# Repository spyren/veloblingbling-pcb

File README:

Electronic Design for the Velo Bling-Bling Project
**************************************************

http://veloblingbling.ch

LED lights for bicycle wheels.
16 multi color LEDs on each side (PCB top- and bottom side).
There are two windows (upper and lower) on each side for display dynamic
information like speed, trip time, trip distance, etc. or static information
like strings and images.

The Printed Circuit Board (PCB) is free hardware.
The PCB is a multi-layer (4 layer) 160 x 30.5 x 1.6 mm FR4 board.
The firmware for the MK22DX256VLF5 MCU is also on GitHub:
https://github.com/spyren/veloblingbling-mcu

There is also an optional Bluetooth Low Energy (Smart) subsystem on board.
It is a LAIRD BL600-SA module. The Bluetooth application software is on GitHub
too:
https://github.com/spyren/veloblingbling-ble

It is possible to mount die PCB direct onto the wheel spokes but it is better
to use a mounting frame. This frame can be ordered from http://shapeways.com
or you can print it by yourself on 3D printer.
https://github.com/spyren/veloblingbling-frame

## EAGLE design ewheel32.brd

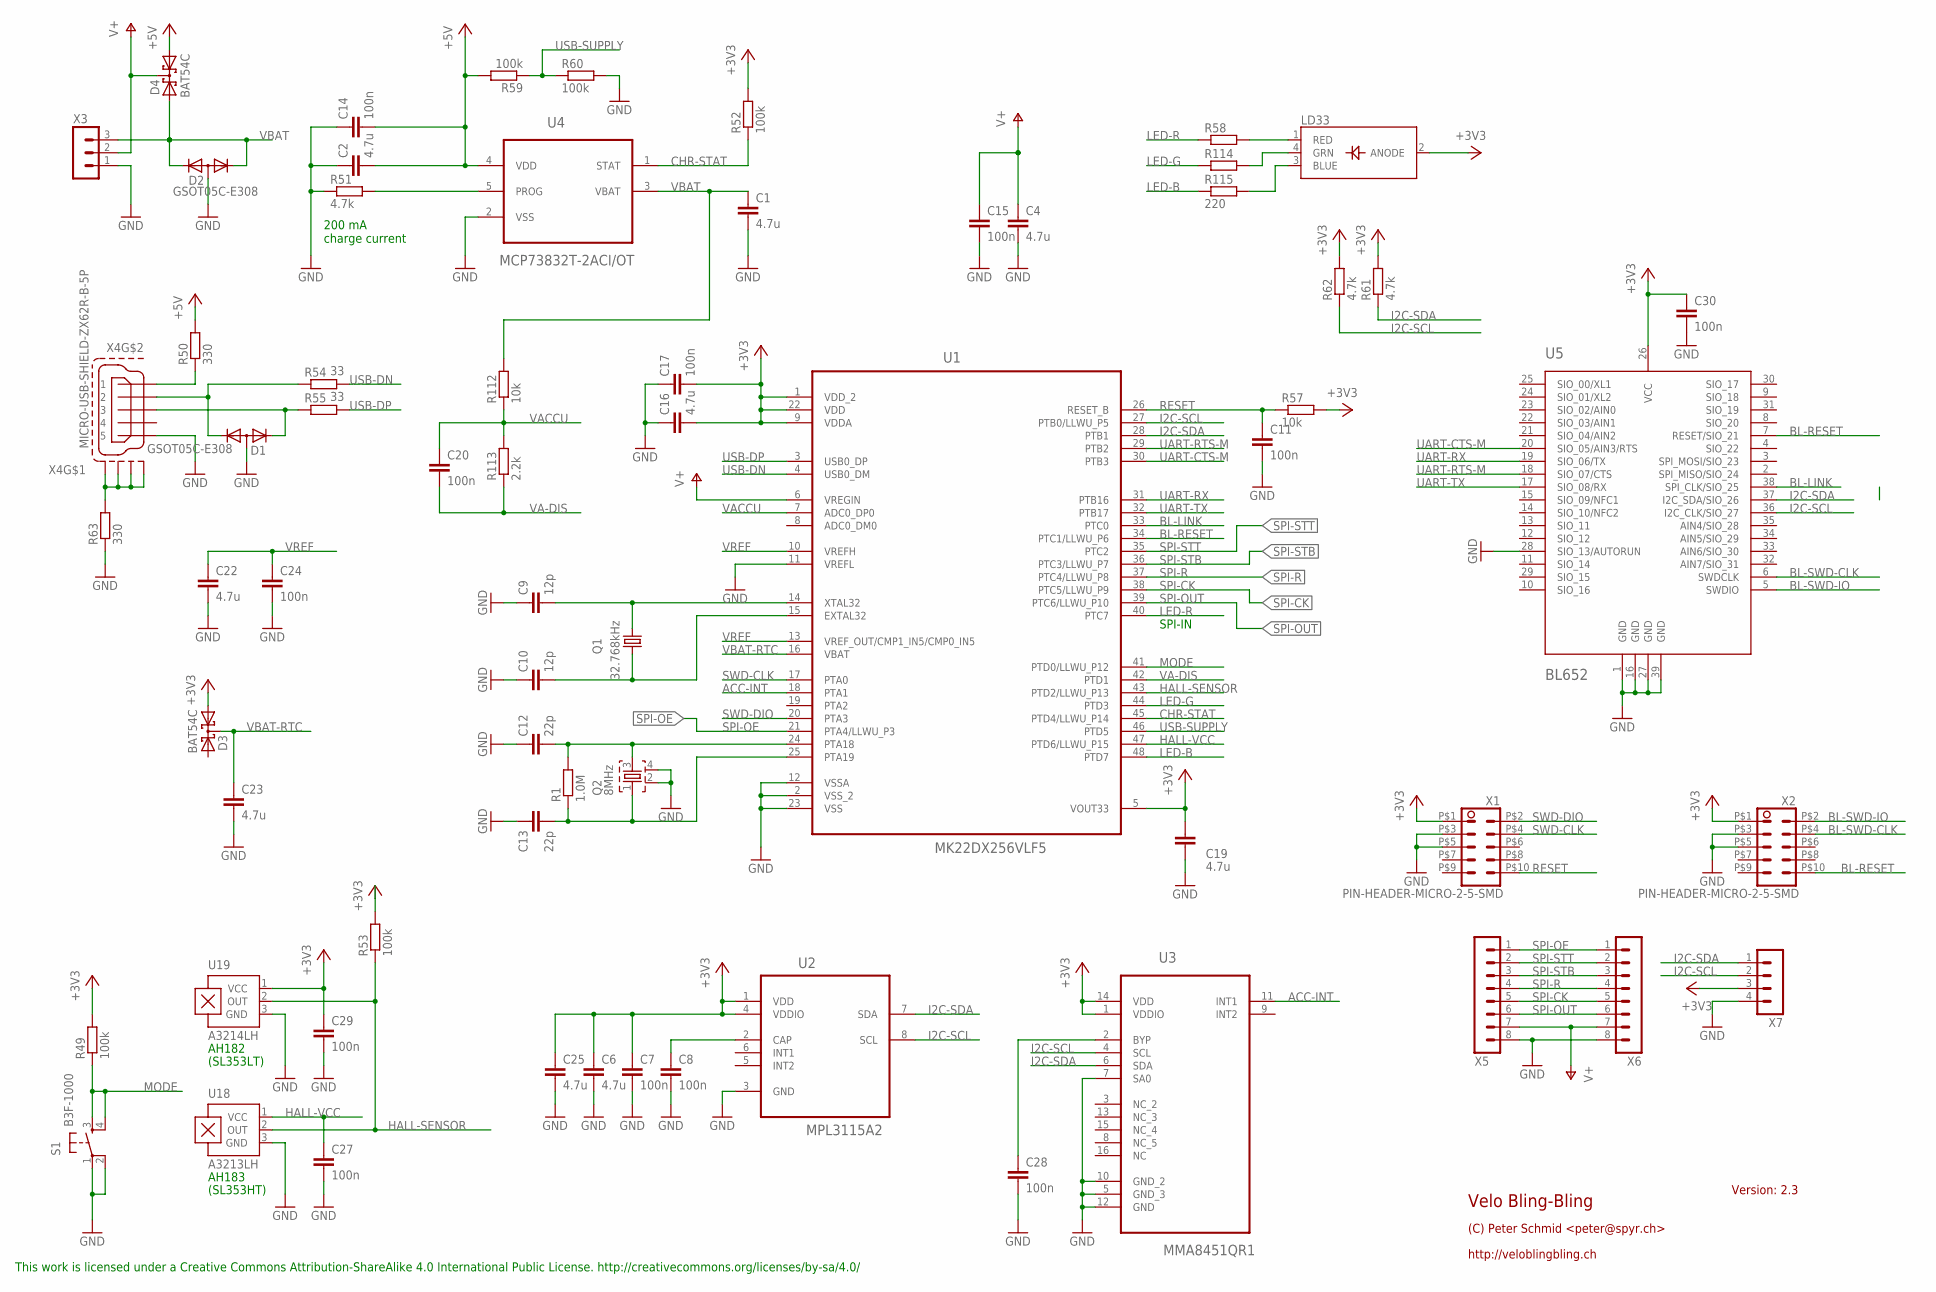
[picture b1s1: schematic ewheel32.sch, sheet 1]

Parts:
C1, C2, C4, C6, C16, C19, C22, C23, C25: 4.7u; C0805
C7, C8, C11, C14, C15, C17, C20, C24, C27, C28, C29, C30: 100n; C0805
C9, C10: 12p; C0805
C12, C13: 22p; C0805
D1, D2: GSOT05C-E308; SOT23
D3, D4: BAT54C; SOT23
LD33: CLV1A-FKB; RGBLED-PLCC4
Q1: 32.768kHz; ABS07
Q2: 8MHz; ABM3B
R1: 1.0M; R0805
R49, R52, R53, R59, R60: 100k; R0805
R50, R63: 330; R1206
R51, R61, R62: 4.7k; R0805
R54, R55: 33; R0805
R57, R112: 10k; R0805
R58, R114, R115: 220; R0805
R113: 2.2k; R0805
S1: B3F-1000; B3S-1000
U1: MK22DX256VLF5; QFP50P900X900X160-48N
U2: MPL3115A2; DFN300X500X120-8N
U3: MMA8451QR1; QFN50P300X300X100-16N
U4: MCP73832T-2ACI/OT; SOT95P280X145-5N
U5: BL652
U18: A3213LH; SOT23-W
U19: A3214LH; SOT23-W
X1, X2: PIN-HEADER-MICRO-2-5-SMD; PIN-HEADER-NICRO-2-5-SMD
X3: MA03-1
X4: MICRO-USB-SHIELD-ZX62R-B-5P; ZX62R-B-5P
X5, X6: MA08-1
X7: MA04-1

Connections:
+3V3: C6.1, C7.1, C16.2, C17.2, C19.1, C25.1, C29.1, C30.1, D3.1 (A1), LD33.2 (ANODE), R49.2, R52.2, R53.2, R57.2, R61.2, R62.2, U1.1 (VDD_2), U1.5 (VOUT33), U1.9 (VDDA), U1.22 (VDD), U2.1 (VDD), U2.4 (VDDIO), U3.1 (VDDIO), U3.14 (VDD), U5.26 (VCC), U19.1 (VCC), X1.P$1 (1), X2.P$1 (1), X7.3
+5V: C2.2, C14.2, D4.1 (A1), R50.2, R59.2, U4.4 (VDD)
ACC-INT: U1.18 (PTA1), U3.11 (INT1)
BL-LINK: U1.33 (PTC0), U5.38 (SPI_CLK/SIO_25)
BL-RESET: U1.34 (PTC1/LLWU_P6), U5.7 (RESET/SIO_21), X2.P$10 (10)
BL-SWD-CLK: U5.6 (SWDCLK), X2.P$4 (4)
BL-SWD-IO: U5.5 (SWDIO), X2.P$2 (2)
CHR-STAT: R52.1, U1.45 (PTD4/LLWU_P14), U4.1 (STAT)
GND: C1.2, C2.1, C4.2, C6.2, C7.2, C8.2, C9.1, C10.1, C11.2, C12.1, C13.1, C14.1, C15.2, C16.1, C17.1, C19.2, C22.2, C23.2, C24.2, C25.2, C27.2, C28.2, C29.2, C30.2, D1.3 (A), D2.3 (A), Q2.2, Q2.4, R51.1, R60.2, R63.1, S1.1, S1.2 (P1), U1.2 (VSS_2), U1.11 (VREFL), U1.12 (VSSA), U1.23 (VSS), U2.3 (GND), U3.5 (GND_3), U3.7 (SA0), U3.10 (GND_2), U3.12 (GND), U4.2 (VSS), U5.1 (GND), U5.16 (GND), U5.27 (GND), U5.28 (SIO_13/AUTORUN), U5.39 (GND), U18.3 (GND), U19.3 (GND), X1.P$3 (3), X1.P$5 (5), X2.P$3 (3), X2.P$5 (5), X3.1, X4.5, X5.8, X6.8, X7.4; also elsewhere on the board
HALL-SENSOR: R53.1, U1.43 (PTD2/LLWU_P13), U18.2 (OUT), U19.2 (OUT)
HALL-VCC: C27.1, U1.47 (PTD6/LLWU_P15), U18.1 (VCC)
I2C-SCL: R62.1, U1.27 (PTB0/LLWU_P5), U2.8 (SCL), U3.4 (SCL), U5.36 (I2C_CLK/SIO_27), X7.2
I2C-SDA: R61.1, U1.28 (PTB1), U2.7 (SDA), U3.6 (SDA), U5.37 (I2C_SDA/SIO_26), X7.1
LED-B: R115.1, U1.48 (PTD7)
LED-G: R114.1, U1.44 (PTD3)
LED-R: R58.1, U1.40 (PTC7)
MODE: R49.1, S1.3 (S), S1.4 (S1), U1.41 (PTD0/LLWU_P12)
unnamed: C12.2, Q2.3, R1.2, U1.24 (PTA18)
unnamed: C13.2, Q2.1, R1.1, U1.25 (PTA19)
unnamed: C28.1, U3.2 (BYP)
unnamed: R51.2, U4.5 (PROG)
unnamed: LD33.4 (GRN), R114.2
unnamed: LD33.1 (RED), R58.2
unnamed: LD33.3 (BLUE), R115.2
unnamed: R63.2, X4.M1 (S1), X4.M2 (S2), X4.M3 (S3), X4.M4 (S4)
unnamed: C8.1, U2.2 (CAP)
unnamed: R50.1, X4.1
unnamed: D1.1 (K1), R54.1, X4.2
unnamed: D1.2 (K2), R55.1, X4.3
unnamed: C9.2, Q1.P$2 (2), U1.14 (XTAL32)
unnamed: C10.2, Q1.P$1 (1), U1.15 (EXTAL32)
RESET: C11.1, R57.1, U1.26 (RESET_B), X1.P$10 (10)
SPI-CK: U1.38 (PTC5/LLWU_P9), X5.5, X6.5; also elsewhere on the board
SPI-OE: U1.21 (PTA4/LLWU_P3), X5.1, X6.1; also elsewhere on the board
SPI-OUT: U1.39 (PTC6/LLWU_P10), X5.6, X6.6; also elsewhere on the board
SPI-R: U1.37 (PTC4/LLWU_P8), X5.4, X6.4; also elsewhere on the board
SPI-STB: U1.36 (PTC3/LLWU_P7), X5.3, X6.3; also elsewhere on the board
SPI-STT: U1.35 (PTC2), X5.2, X6.2; also elsewhere on the board
SWD-CLK: U1.17 (PTA0), X1.P$4 (4)
SWD-DIO: U1.20 (PTA3), X1.P$2 (2)
UART-CTS-M: U1.30 (PTB3), U5.20 (SIO_05/AIN3/RTS)
UART-RTS-M: U1.29 (PTB2), U5.18 (SIO_07/CTS)
UART-RX: U1.31 (PTB16), U5.19 (SIO_06/TX)
UART-TX: U1.32 (PTB17), U5.17 (SIO_08/RX)
USB-DN: R54.2, U1.4 (USB0_DM)
USB-DP: R55.2, U1.3 (USB0_DP)
USB-SUPPLY: R59.1, R60.1, U1.46 (PTD5)
V+: C4.1, C15.1, D4.3 (CC), U1.6 (VREGIN), X3.2, X5.7, X6.7; also elsewhere on the board
VA-DIS: C20.2, R113.1, U1.42 (PTD1)
VACCU: C20.1, R112.1, R113.2, U1.7 (ADC0_DP0)
VBAT: C1.1, D2.1 (K1), D2.2 (K2), D4.2 (A2), R112.2, U4.3 (VBAT), X3.3
VBAT-RTC: C23.1, D3.3 (CC), U1.16 (VBAT)
VREF: C22.1, C24.1, U1.10 (VREFH), U1.13 (VREF_OUT/CMP1_IN5/CMP0_IN5)

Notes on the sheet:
200 mA charge current
SPI-IN
(SL353LT)
(SL353HT)
AH182
AH183

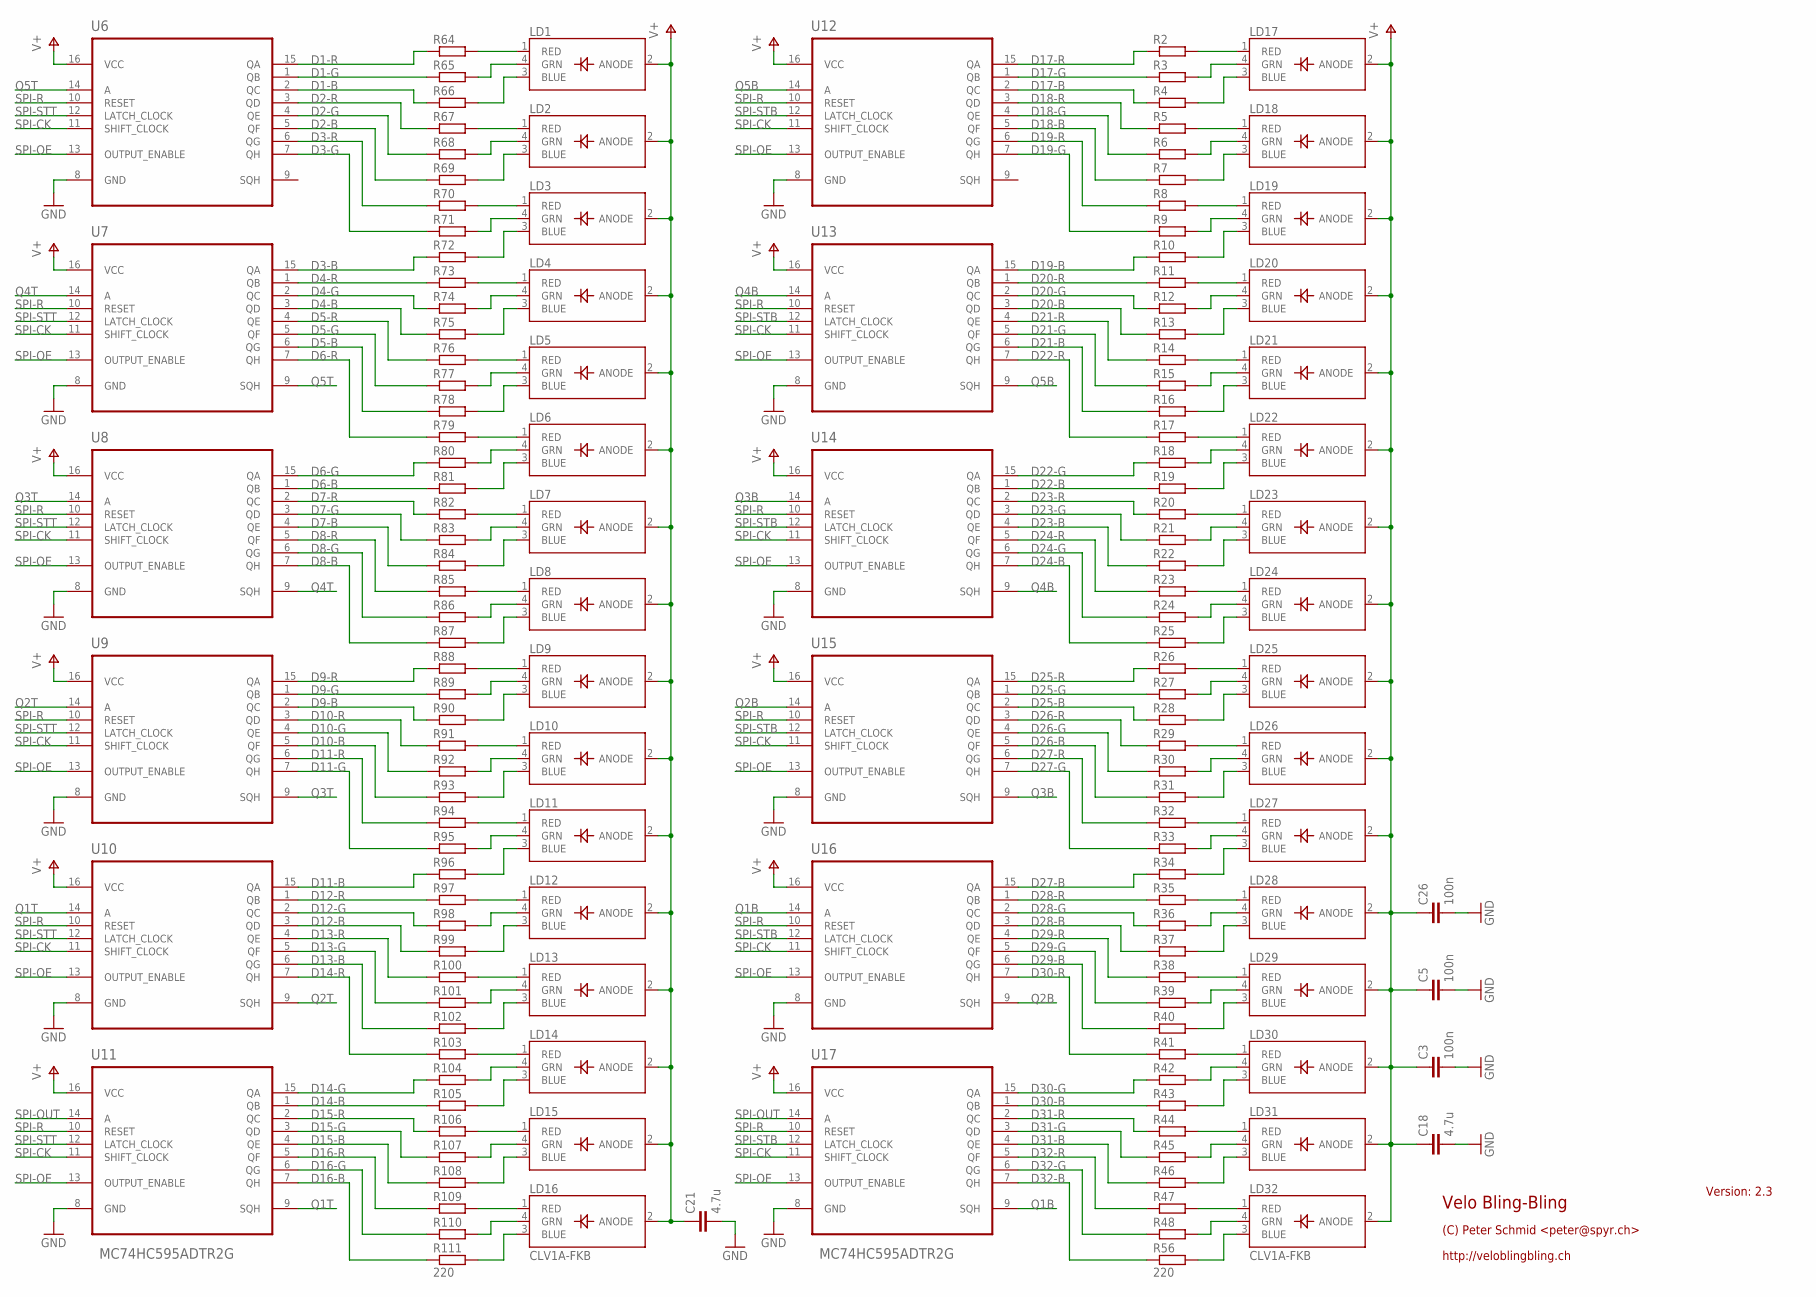
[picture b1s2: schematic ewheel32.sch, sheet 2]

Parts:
C3, C5, C26: 100n; C0805
C18, C21: 4.7u; C0805
LD1, LD2, LD3, LD4, LD5, LD6, LD7, LD8, LD9, LD10, LD11, LD12, LD13, LD14, LD15, LD16, LD17, LD18, LD19, LD20, LD21, LD22, LD23, LD24, LD25, LD26, LD27, LD28, LD29, LD30, LD31, LD32: CLV1A-FKB; RGBLED-PLCC4
R2, R3, R4, R5, R6, R7, R8, R9, R10, R11, R12, R13, R14, R15, R16, R17, R18, R19, R20, R21, R22, R23, R24, R25, R26, R27, R28, R29, R30, R31, R32, R33, R34, R35, R36, R37, R38, R39, R40, R41, R42, R43, R44, R45, R46, R47, R48, R56, R64, R65, R66, R67, R68, R69, R70, R71, R72, R73, R74, R75, R76, R77, R78, R79, R80, R81, R82, R83, R84, R85, R86, R87, R88, R89, R90, R91, R92, R93, R94, R95, R96, R97, R98, R99, R100, R101, R102, R103, R104, R105, R106, R107, R108, R109, R110, R111: 220; R0805
U6, U7, U8, U9, U10, U11, U12, U13, U14, U15, U16, U17: MC74HC595ADTR2G; SOP65P640X120-16N

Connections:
D1-B: R66.1, U6.2 (QC)
D1-G: R65.1, U6.1 (QB)
D1-R: R64.1, U6.15 (QA)
D2-B: R69.1, U6.5 (QF)
D2-G: R68.1, U6.4 (QE)
D2-R: R67.1, U6.3 (QD)
D3-B: R72.1, U7.15 (QA)
D3-G: R71.1, U6.7 (QH)
D3-R: R70.1, U6.6 (QG)
D4-B: R75.1, U7.3 (QD)
D4-G: R74.1, U7.2 (QC)
D4-R: R73.1, U7.1 (QB)
D5-B: R78.1, U7.6 (QG)
D5-G: R77.1, U7.5 (QF)
D5-R: R76.1, U7.4 (QE)
D6-B: R81.1, U8.1 (QB)
D6-G: R80.1, U8.15 (QA)
D6-R: R79.1, U7.7 (QH)
D7-B: R84.1, U8.4 (QE)
D7-G: R83.1, U8.3 (QD)
D7-R: R82.1, U8.2 (QC)
D8-B: R87.1, U8.7 (QH)
D8-G: R86.1, U8.6 (QG)
D8-R: R85.1, U8.5 (QF)
D9-B: R90.1, U9.2 (QC)
D9-G: R89.1, U9.1 (QB)
D9-R: R88.1, U9.15 (QA)
D10-B: R93.1, U9.5 (QF)
D10-G: R92.1, U9.4 (QE)
D10-R: R91.1, U9.3 (QD)
D11-B: R96.1, U10.15 (QA)
D11-G: R95.1, U9.7 (QH)
D11-R: R94.1, U9.6 (QG)
D12-B: R99.1, U10.3 (QD)
D12-G: R98.1, U10.2 (QC)
D12-R: R97.1, U10.1 (QB)
D13-B: R102.1, U10.6 (QG)
D13-G: R101.1, U10.5 (QF)
D13-R: R100.1, U10.4 (QE)
D14-B: R105.1, U11.1 (QB)
D14-G: R104.1, U11.15 (QA)
D14-R: R103.1, U10.7 (QH)
D15-B: R108.1, U11.4 (QE)
D15-G: R107.1, U11.3 (QD)
D15-R: R106.1, U11.2 (QC)
D16-B: R111.1, U11.7 (QH)
D16-G: R110.1, U11.6 (QG)
D16-R: R109.1, U11.5 (QF)
D17-B: R4.1, U12.2 (QC)
D17-G: R3.1, U12.1 (QB)
D17-R: R2.1, U12.15 (QA)
D18-B: R7.1, U12.5 (QF)
D18-G: R6.1, U12.4 (QE)
D18-R: R5.1, U12.3 (QD)
D19-B: R10.1, U13.15 (QA)
D19-G: R9.1, U12.7 (QH)
D19-R: R8.1, U12.6 (QG)
D20-B: R13.1, U13.3 (QD)
D20-G: R12.1, U13.2 (QC)
D20-R: R11.1, U13.1 (QB)
D21-B: R16.1, U13.6 (QG)
D21-G: R15.1, U13.5 (QF)
D21-R: R14.1, U13.4 (QE)
D22-B: R19.1, U14.1 (QB)
D22-G: R18.1, U14.15 (QA)
D22-R: R17.1, U13.7 (QH)
D23-B: R22.1, U14.4 (QE)
D23-G: R21.1, U14.3 (QD)
D23-R: R20.1, U14.2 (QC)
D24-B: R25.1, U14.7 (QH)
D24-G: R24.1, U14.6 (QG)
D24-R: R23.1, U14.5 (QF)
D25-B: R28.1, U15.2 (QC)
D25-G: R27.1, U15.1 (QB)
D25-R: R26.1, U15.15 (QA)
D26-B: R31.1, U15.5 (QF)
D26-G: R30.1, U15.4 (QE)
D26-R: R29.1, U15.3 (QD)
D27-B: R34.1, U16.15 (QA)
D27-G: R33.1, U15.7 (QH)
D27-R: R32.1, U15.6 (QG)
D28-B: R37.1, U16.3 (QD)
D28-G: R36.1, U16.2 (QC)
D28-R: R35.1, U16.1 (QB)
D29-B: R40.1, U16.6 (QG)
D29-G: R39.1, U16.5 (QF)
D29-R: R38.1, U16.4 (QE)
D30-B: R43.1, U17.1 (QB)
D30-G: R42.1, U17.15 (QA)
D30-R: R41.1, U16.7 (QH)
D31-B: R46.1, U17.4 (QE)
D31-G: R45.1, U17.3 (QD)
D31-R: R44.1, U17.2 (QC)
D32-B: R56.1, U17.7 (QH)
D32-G: R48.1, U17.6 (QG)
D32-R: R47.1, U17.5 (QF)
GND: C3.2, C5.2, C18.2, C21.2, C26.2, U6.8 (GND), U7.8 (GND), U8.8 (GND), U9.8 (GND), U10.8 (GND), U11.8 (GND), U12.8 (GND), U13.8 (GND), U14.8 (GND), U15.8 (GND), U16.8 (GND), U17.8 (GND); also elsewhere on the board
unnamed: LD17.4 (GRN), R3.2
unnamed: LD17.1 (RED), R2.2
unnamed: LD17.3 (BLUE), R4.2
unnamed: LD18.4 (GRN), R6.2
unnamed: LD18.1 (RED), R5.2
unnamed: LD18.3 (BLUE), R7.2
unnamed: LD19.4 (GRN), R9.2
unnamed: LD19.1 (RED), R8.2
unnamed: LD19.3 (BLUE), R10.2
unnamed: LD20.4 (GRN), R12.2
unnamed: LD20.1 (RED), R11.2
unnamed: LD20.3 (BLUE), R13.2
unnamed: LD21.4 (GRN), R15.2
unnamed: LD21.1 (RED), R14.2
unnamed: LD21.3 (BLUE), R16.2
unnamed: LD22.4 (GRN), R18.2
unnamed: LD22.1 (RED), R17.2
unnamed: LD22.3 (BLUE), R19.2
unnamed: LD23.4 (GRN), R21.2
unnamed: LD23.1 (RED), R20.2
unnamed: LD23.3 (BLUE), R22.2
unnamed: LD24.4 (GRN), R24.2
unnamed: LD24.1 (RED), R23.2
unnamed: LD24.3 (BLUE), R25.2
unnamed: LD25.4 (GRN), R27.2
unnamed: LD25.1 (RED), R26.2
unnamed: LD25.3 (BLUE), R28.2
unnamed: LD26.4 (GRN), R30.2
unnamed: LD26.1 (RED), R29.2
unnamed: LD26.3 (BLUE), R31.2
unnamed: LD27.4 (GRN), R33.2
unnamed: LD27.1 (RED), R32.2
unnamed: LD27.3 (BLUE), R34.2
unnamed: LD28.4 (GRN), R36.2
unnamed: LD28.1 (RED), R35.2
unnamed: LD1.4 (GRN), R65.2
unnamed: LD1.1 (RED), R64.2
unnamed: LD1.3 (BLUE), R66.2
unnamed: LD2.4 (GRN), R68.2
unnamed: LD2.1 (RED), R67.2
unnamed: LD2.3 (BLUE), R69.2
unnamed: LD3.4 (GRN), R71.2
unnamed: LD3.1 (RED), R70.2
unnamed: LD3.3 (BLUE), R72.2
unnamed: LD4.4 (GRN), R74.2
unnamed: LD4.1 (RED), R73.2
unnamed: LD4.3 (BLUE), R75.2
unnamed: LD5.4 (GRN), R77.2
unnamed: LD5.1 (RED), R76.2
unnamed: LD5.3 (BLUE), R78.2
unnamed: LD6.4 (GRN), R80.2
unnamed: LD6.1 (RED), R79.2
unnamed: LD6.3 (BLUE), R81.2
unnamed: LD7.4 (GRN), R83.2
unnamed: LD7.1 (RED), R82.2
unnamed: LD7.3 (BLUE), R84.2
unnamed: LD8.4 (GRN), R86.2
unnamed: LD8.1 (RED), R85.2
unnamed: LD8.3 (BLUE), R87.2
unnamed: LD9.4 (GRN), R89.2
unnamed: LD9.1 (RED), R88.2
unnamed: LD9.3 (BLUE), R90.2
unnamed: LD10.4 (GRN), R92.2
unnamed: LD10.1 (RED), R91.2
unnamed: LD10.3 (BLUE), R93.2
unnamed: LD11.4 (GRN), R95.2
unnamed: LD11.1 (RED), R94.2
unnamed: LD11.3 (BLUE), R96.2
unnamed: LD12.4 (GRN), R98.2
unnamed: LD12.1 (RED), R97.2
unnamed: LD12.3 (BLUE), R99.2
unnamed: LD13.4 (GRN), R101.2
unnamed: LD13.1 (RED), R100.2
unnamed: LD13.3 (BLUE), R102.2
unnamed: LD14.4 (GRN), R104.2
unnamed: LD14.1 (RED), R103.2
unnamed: LD14.3 (BLUE), R105.2
unnamed: LD15.4 (GRN), R107.2
unnamed: LD15.1 (RED), R106.2
unnamed: LD15.3 (BLUE), R108.2
unnamed: LD16.4 (GRN), R110.2
unnamed: LD16.1 (RED), R109.2
unnamed: LD16.3 (BLUE), R111.2
unnamed: LD28.3 (BLUE), R37.2
unnamed: LD29.4 (GRN), R39.2
unnamed: LD29.1 (RED), R38.2
unnamed: LD29.3 (BLUE), R40.2
unnamed: LD30.4 (GRN), R42.2
unnamed: LD30.1 (RED), R41.2
unnamed: LD30.3 (BLUE), R43.2
unnamed: LD31.4 (GRN), R45.2
unnamed: LD31.1 (RED), R44.2
unnamed: LD31.3 (BLUE), R46.2
unnamed: LD32.4 (GRN), R48.2
unnamed: LD32.1 (RED), R47.2
unnamed: LD32.3 (BLUE), R56.2
Q1B: U16.14 (A), U17.9 (SQH)
Q1T: U10.14 (A), U11.9 (SQH)
Q2B: U15.14 (A), U16.9 (SQH)
Q2T: U9.14 (A), U10.9 (SQH)
Q3B: U14.14 (A), U15.9 (SQH)
Q3T: U8.14 (A), U9.9 (SQH)
Q4B: U13.14 (A), U14.9 (SQH)
Q4T: U7.14 (A), U8.9 (SQH)
Q5B: U12.14 (A), U13.9 (SQH)
Q5T: U6.14 (A), U7.9 (SQH)
SPI-CK: U6.11 (SHIFT_CLOCK), U7.11 (SHIFT_CLOCK), U8.11 (SHIFT_CLOCK), U9.11 (SHIFT_CLOCK), U10.11 (SHIFT_CLOCK), U11.11 (SHIFT_CLOCK), U12.11 (SHIFT_CLOCK), U13.11 (SHIFT_CLOCK), U14.11 (SHIFT_CLOCK), U15.11 (SHIFT_CLOCK), U16.11 (SHIFT_CLOCK), U17.11 (SHIFT_CLOCK); also elsewhere on the board
SPI-OE: U6.13 (OUTPUT_ENABLE), U7.13 (OUTPUT_ENABLE), U8.13 (OUTPUT_ENABLE), U9.13 (OUTPUT_ENABLE), U10.13 (OUTPUT_ENABLE), U11.13 (OUTPUT_ENABLE), U12.13 (OUTPUT_ENABLE), U13.13 (OUTPUT_ENABLE), U14.13 (OUTPUT_ENABLE), U15.13 (OUTPUT_ENABLE), U16.13 (OUTPUT_ENABLE), U17.13 (OUTPUT_ENABLE); also elsewhere on the board
SPI-OUT: U11.14 (A), U17.14 (A); also elsewhere on the board
SPI-R: U6.10 (RESET), U7.10 (RESET), U8.10 (RESET), U9.10 (RESET), U10.10 (RESET), U11.10 (RESET), U12.10 (RESET), U13.10 (RESET), U14.10 (RESET), U15.10 (RESET), U16.10 (RESET), U17.10 (RESET); also elsewhere on the board
SPI-STB: U12.12 (LATCH_CLOCK), U13.12 (LATCH_CLOCK), U14.12 (LATCH_CLOCK), U15.12 (LATCH_CLOCK), U16.12 (LATCH_CLOCK), U17.12 (LATCH_CLOCK); also elsewhere on the board
SPI-STT: U6.12 (LATCH_CLOCK), U7.12 (LATCH_CLOCK), U8.12 (LATCH_CLOCK), U9.12 (LATCH_CLOCK), U10.12 (LATCH_CLOCK), U11.12 (LATCH_CLOCK); also elsewhere on the board
V+: C3.1, C5.1, C18.1, C21.1, C26.1, LD1.2 (ANODE), LD2.2 (ANODE), LD3.2 (ANODE), LD4.2 (ANODE), LD5.2 (ANODE), LD6.2 (ANODE), LD7.2 (ANODE), LD8.2 (ANODE), LD9.2 (ANODE), LD10.2 (ANODE), LD11.2 (ANODE), LD12.2 (ANODE), LD13.2 (ANODE), LD14.2 (ANODE), LD15.2 (ANODE), LD16.2 (ANODE), LD17.2 (ANODE), LD18.2 (ANODE), LD19.2 (ANODE), LD20.2 (ANODE), LD21.2 (ANODE), LD22.2 (ANODE), LD23.2 (ANODE), LD24.2 (ANODE), LD25.2 (ANODE), LD26.2 (ANODE), LD27.2 (ANODE), LD28.2 (ANODE), LD29.2 (ANODE), LD30.2 (ANODE), LD31.2 (ANODE), LD32.2 (ANODE), U6.16 (VCC), U7.16 (VCC), U8.16 (VCC), U9.16 (VCC), U10.16 (VCC), U11.16 (VCC), U12.16 (VCC), U13.16 (VCC), U14.16 (VCC), U15.16 (VCC), U16.16 (VCC), U17.16 (VCC); also elsewhere on the board

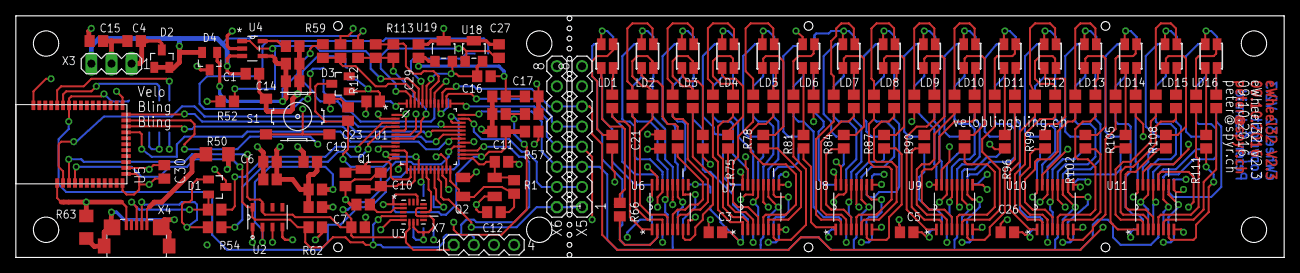
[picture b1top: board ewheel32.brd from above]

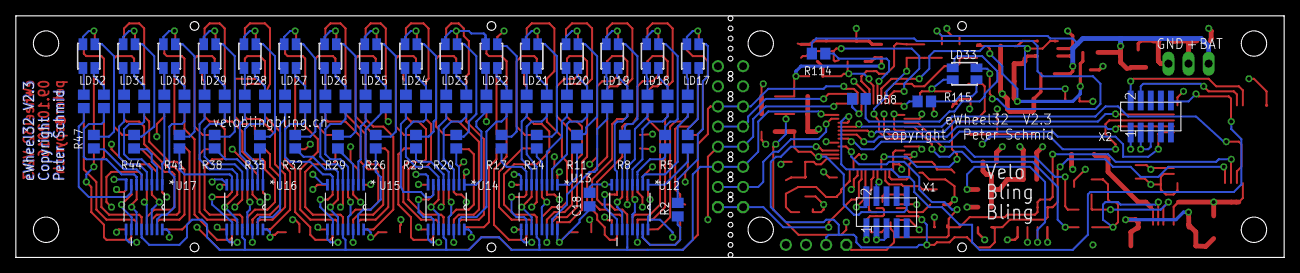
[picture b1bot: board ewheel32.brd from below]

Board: 4 copper layers, 160.0 x 30.5 mm, 211 parts (77 on the bottom side), 255 nets.

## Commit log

2015-09-23 Version 1.3, Betatest
2015-10-06 Schottky diode for charger
2016-05-23 Intermediate version. Do not use.
2016-05-23 Version 1.4. BAT/VCC connector wrong.
2016-05-23 VBAT and V+ are fixed.
2016-05-24 README and LICENSE added.
2016-07-11 State RGB LED. Second Hall Sensor (ultra low power to wake up from deep sleep). Breakable PCB (MCU part / LED part). Pin head for I2C and SPI.
2016-11-12 New Bluetooth Low Energy module BL652

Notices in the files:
ewheel32.sch:
COPYRIGHT: This work is licensed under a Creative Commons Attribution-ShareAlike 4.0 International Public License. http://creativecommons.org/licenses/by-sa/4.0
